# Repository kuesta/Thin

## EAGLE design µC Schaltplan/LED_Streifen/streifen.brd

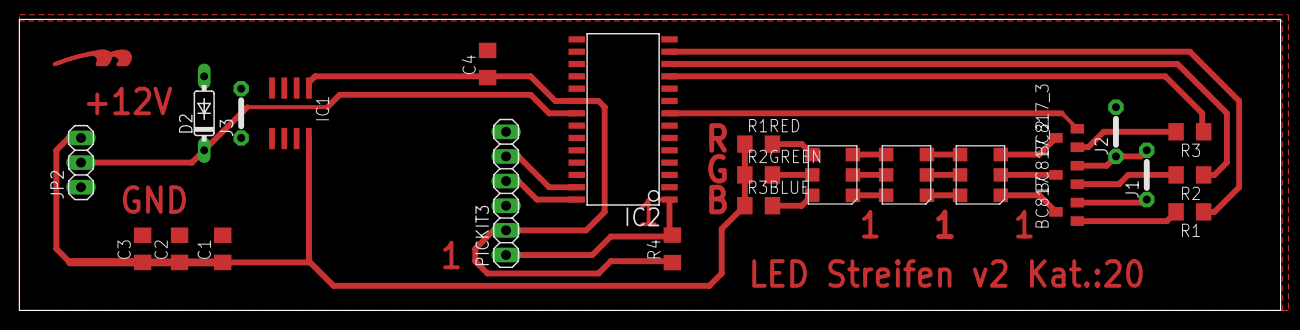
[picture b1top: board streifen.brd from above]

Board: 2 copper layers, 130.0 x 30.0 mm, 26 parts (0 on the bottom side), 27 nets.

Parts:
BC817, BC817_2, BC817_3: BC847SMD; SOT23
C1, C2, C3, C4: 100nF; C1206
D2: DO35-7
IC1: 78L05SMD; SO08
IC2: PIC18F2550_28W; SO28W
J1, J2, J3: J5MM; 05
JP2: 1X03
LED1, LED2, LED3: LP6-EWN1-03-N3; PLCC6
PICKIT3: 1X06
R1, R2, R3, R4: 1,2k; R1206
R1RED: 270; R1206
R2GREEN, R3BLUE: 100; R1206
U$1: LOGOTOP_8

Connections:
GND: BC817_3.2, C1.2, C2.2, C3.2, C4.2, D2.A, IC1.2, IC1.3, IC1.6, IC1.7, IC2.8, IC2.9, IC2.19, J2.2, J3.1, J3.2, JP2.1, PICKIT3.3
unnamed: BC817_3.3, LED1.PAD4
unnamed: IC2.13, R1.1
unnamed: D2.C, IC2.21, JP2.2
unnamed: IC2.1, PICKIT3.1, R4.2
unnamed: BC817_2.3, LED1.PAD5
unnamed: BC817.3, LED1.PAD6
unnamed: C4.1, IC1.1, IC2.20, PICKIT3.2, R4.1
unnamed: IC2.12, R2.1
unnamed: IC2.11, R3.1
unnamed: LED1.PAD3, LED2.PAD6
unnamed: LED1.PAD2, LED2.PAD5
unnamed: LED1.PAD1, LED2.PAD4
unnamed: LED2.PAD3, LED3.PAD6
unnamed: LED2.PAD2, LED3.PAD5
unnamed: LED2.PAD1, LED3.PAD4
unnamed: C1.1, C2.1, C3.1, IC1.8, JP2.3, R1RED.1, R2GREEN.1, R3BLUE.1
unnamed: LED3.PAD1, R1RED.2
unnamed: LED3.PAD2, R2GREEN.2
unnamed: LED3.PAD3, R3BLUE.2
unnamed: BC817.1, R1.2
unnamed: BC817_2.1, R2.2
unnamed: BC817_3.1, R3.2
unnamed: IC2.28, PICKIT3.4
unnamed: IC2.27, PICKIT3.5
unnamed: BC817_2.2, J1.2, J2.1
unnamed: BC817.2, J1.1

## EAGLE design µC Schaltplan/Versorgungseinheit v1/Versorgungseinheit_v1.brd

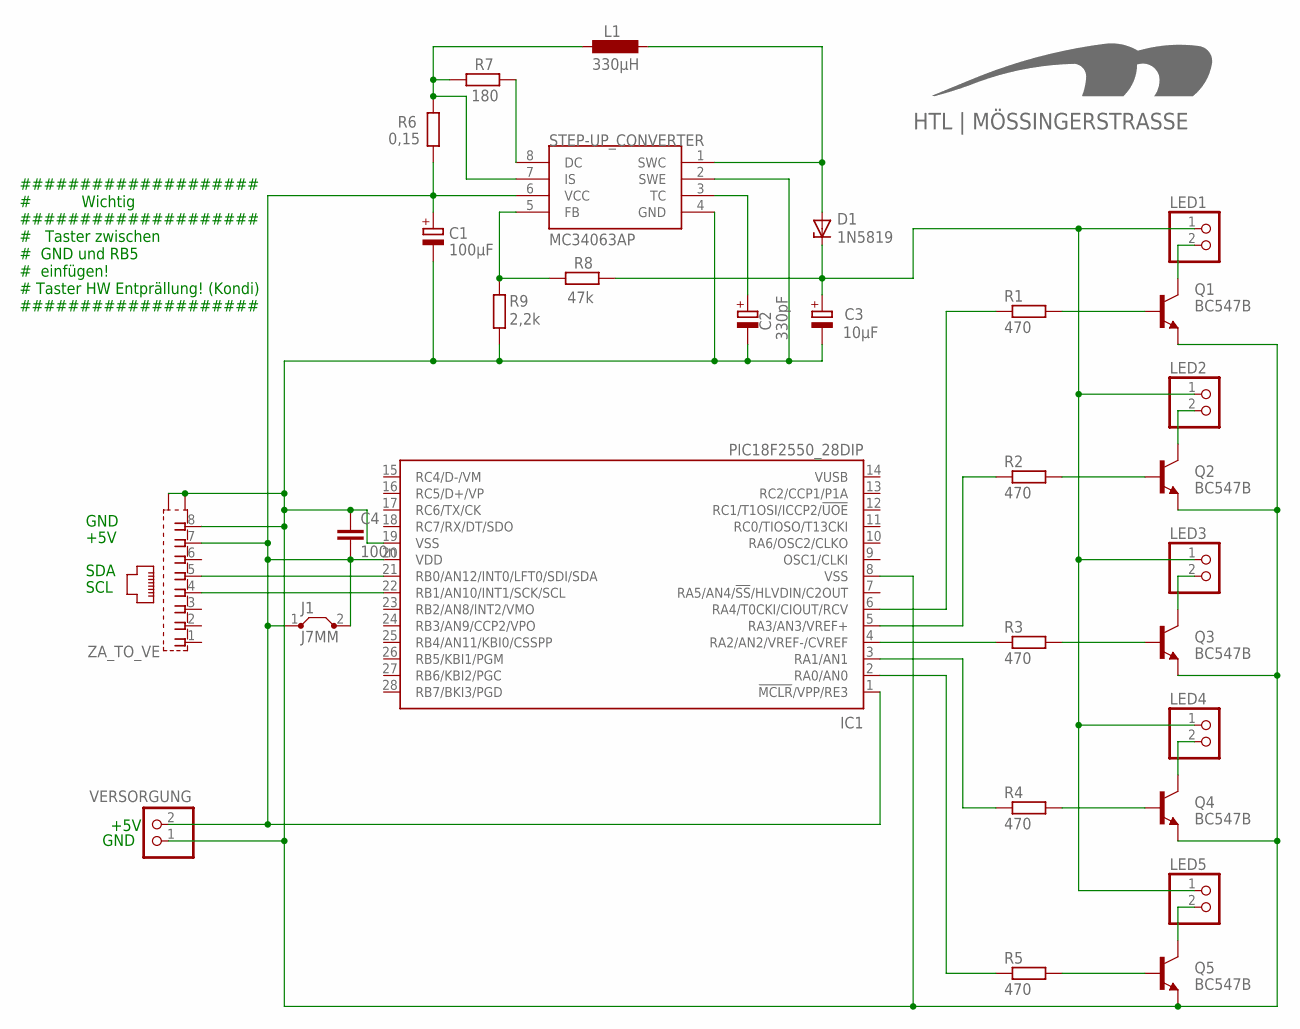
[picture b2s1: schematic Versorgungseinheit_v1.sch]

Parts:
C1: 100µF; E5-8,5
C2: 330pF; E5-8,5
C3: 10µF; E5-8,5
C4: 100n; C050-025X075
D1: 1N5819; DO41Z10
IC1: PIC18F2550_28DIP; DIL28-3
J1: J7MM; 07
L1: 330µH; 0207/10
LED1, LED2, LED3, LED4, LED5: PINHD-1X2; 1X02
Q1, Q2, Q3, Q4, Q5: BC547B; TO92
R1, R2, R3, R4, R5: 470; 0207/10
R6: 0,15; R1206
R7: 180; 0207/10
R8: 47k; 0207/10
R9: 2,2k; 0207/10
STEP-UP_CONVERTER: MC34063AP; DIL08
U$2: HTL_LOGOBOT_15MM; LOGOBOT_15
VERSORGUNG: PINHD-1X2; 1X02
ZA_TO_VE: 555141-1; 555153-1

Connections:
unnamed: IC1.2 (RA0/AN0), R5.1
unnamed: IC1.3 (RA1/AN1), R4.1
unnamed: IC1.6 (RA4/T0CKI/CIOUT/RCV), R1.1
unnamed: IC1.4 (RA2/AN2/VREF-/CVREF), R3.1
unnamed: C3.+, D1.C, LED1.1, LED2.1, LED3.1, LED4.1, LED5.1, R8.1
unnamed: IC1.5 (RA3/AN3/VREF+), R2.1
unnamed: IC1.22 (RB1/AN10/INT1/SCK/SCL), ZA_TO_VE.4
unnamed: Q1.2 (B), R1.2
unnamed: Q2.2 (B), R2.2
unnamed: Q3.2 (B), R3.2
unnamed: Q4.2 (B), R4.2
unnamed: Q5.2 (B), R5.2
unnamed: LED1.2, Q1.3 (C)
unnamed: LED2.2, Q2.3 (C)
unnamed: LED3.2, Q3.3 (C)
unnamed: LED4.2, Q4.3 (C)
unnamed: LED5.2, Q5.3 (C)
unnamed: L1.2, R6.2, R7.2, STEP-UP_CONVERTER.7 (IS)
unnamed: R7.1, STEP-UP_CONVERTER.8 (DC)
unnamed: D1.A, L1.1, STEP-UP_CONVERTER.1 (SWC)
unnamed: R8.2, R9.1, STEP-UP_CONVERTER.5 (FB)
unnamed: C2.+, STEP-UP_CONVERTER.3 (TC)
SDA: IC1.21 (RB0/AN12/INT0/LFT0/SDI/SDA), ZA_TO_VE.5
VDD: C1.+, C4.2, IC1.1 (!MCLR!/VPP/RE3), IC1.20 (VDD), J1.1, J1.2, R6.1, STEP-UP_CONVERTER.6 (VCC), VERSORGUNG.2, ZA_TO_VE.7
VSS: C1.-, C2.-, C3.-, C4.1, IC1.8 (VSS), IC1.19 (VSS), Q1.1 (E), Q2.1 (E), Q3.1 (E), Q4.1 (E), Q5.1 (E), R9.2, STEP-UP_CONVERTER.2 (SWE), STEP-UP_CONVERTER.4 (GND), VERSORGUNG.1, ZA_TO_VE.8, ZA_TO_VE.G1 (S1), ZA_TO_VE.G2 (S2)

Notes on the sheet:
GND
+5V
SCL
SDA
#################### # Wichtig #################### # Taster zwischen # GND und RB5 # einfügen! # Taster HW Entprällung! (Kondi) ####################

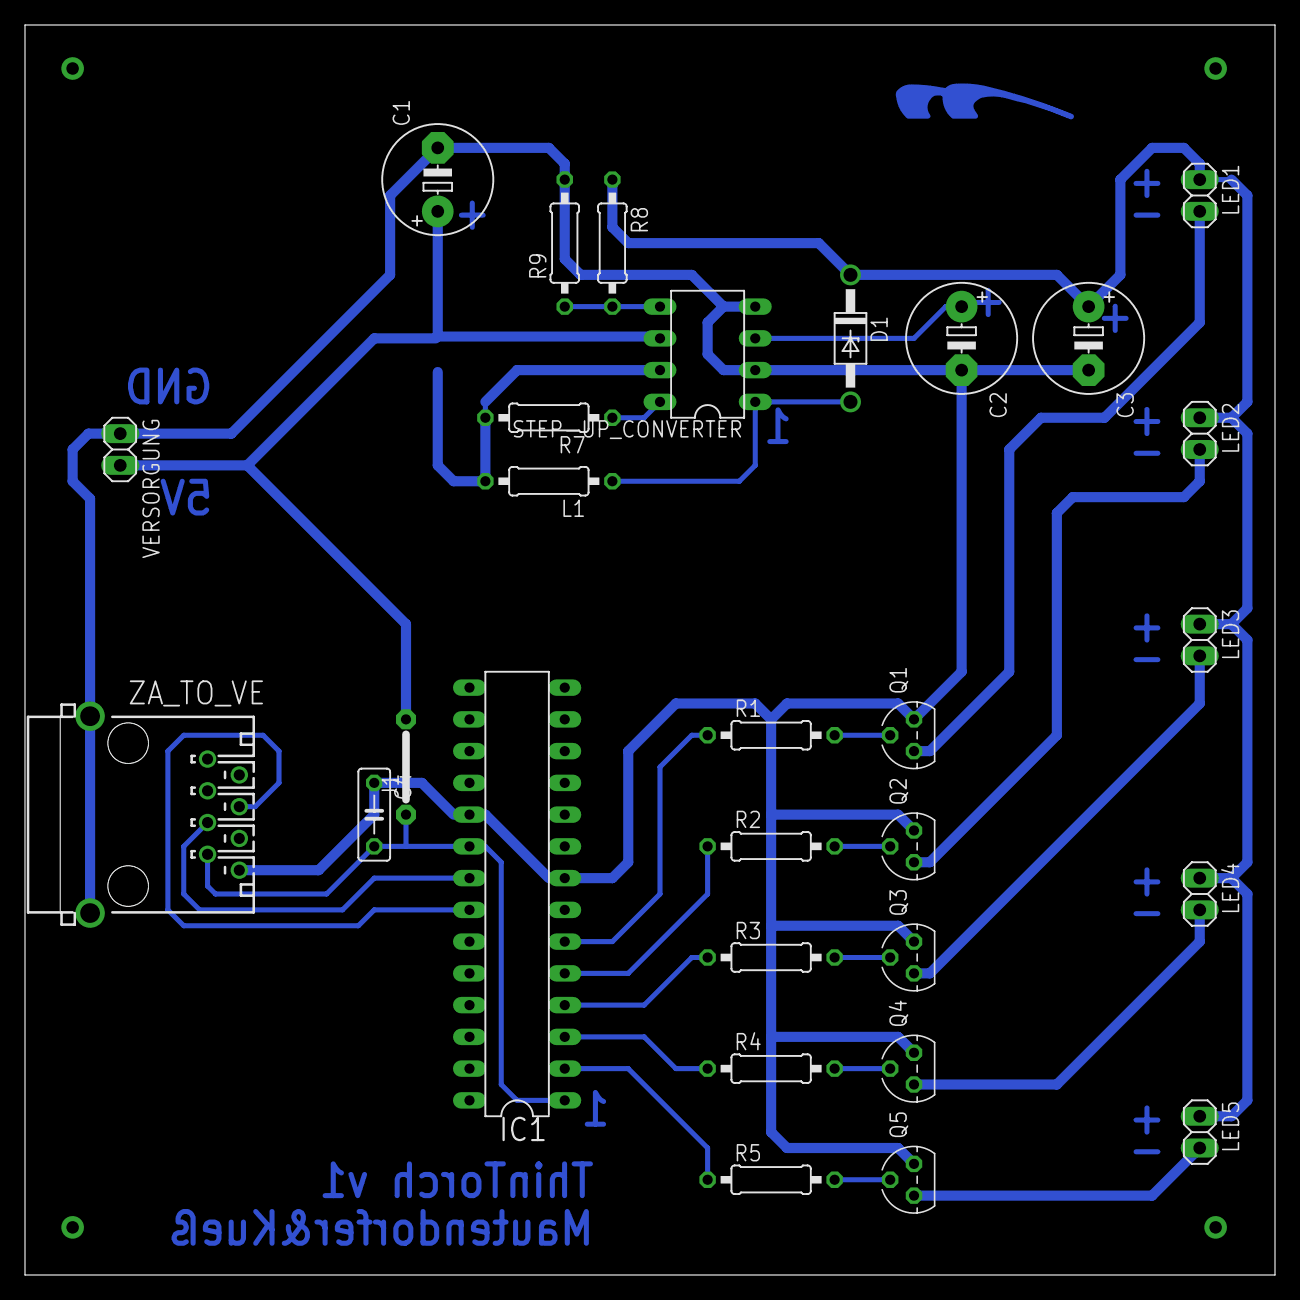
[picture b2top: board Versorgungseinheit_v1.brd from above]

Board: 2 copper layers, 100.0 x 100.0 mm, 31 parts (1 on the bottom side), 25 nets.

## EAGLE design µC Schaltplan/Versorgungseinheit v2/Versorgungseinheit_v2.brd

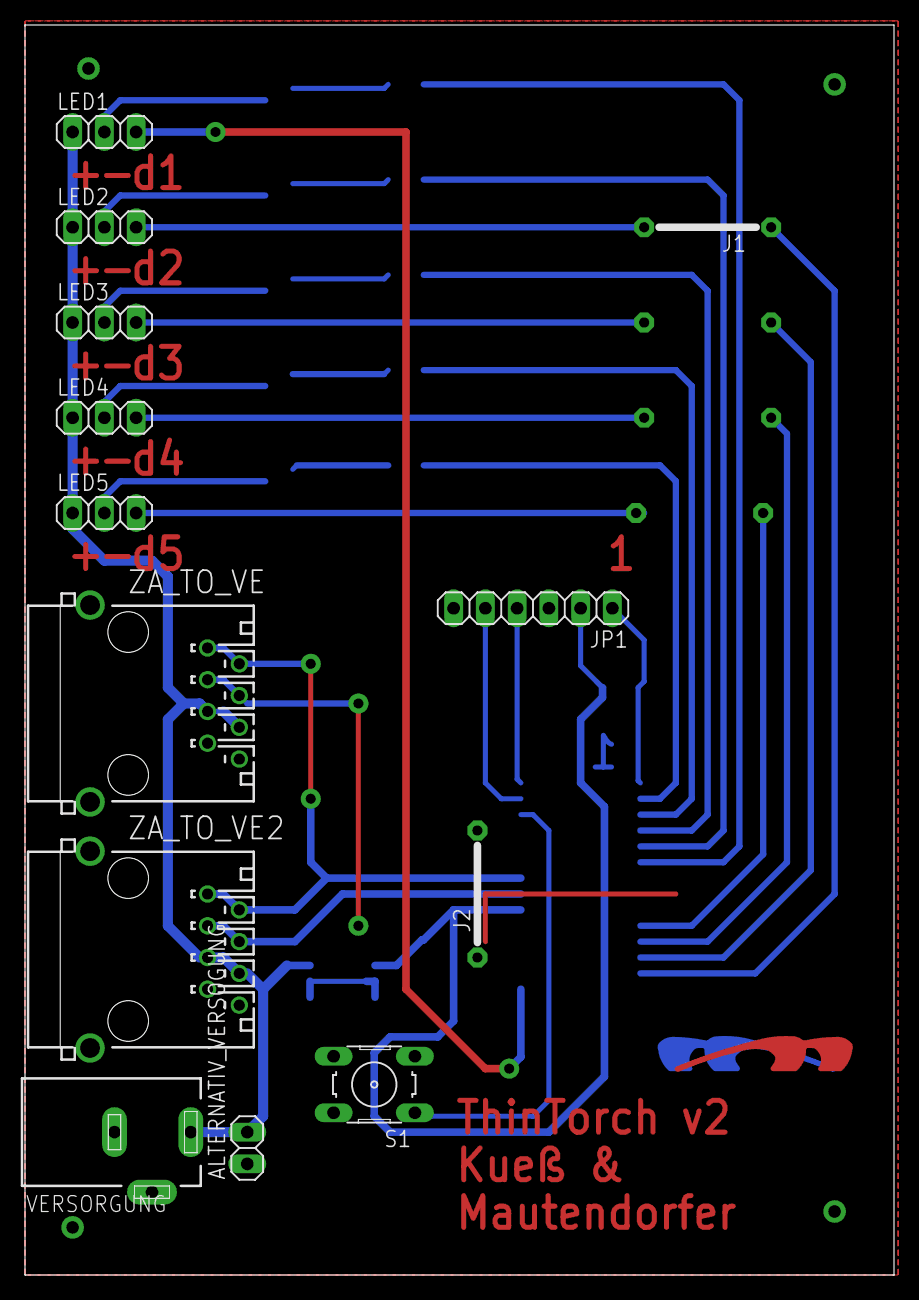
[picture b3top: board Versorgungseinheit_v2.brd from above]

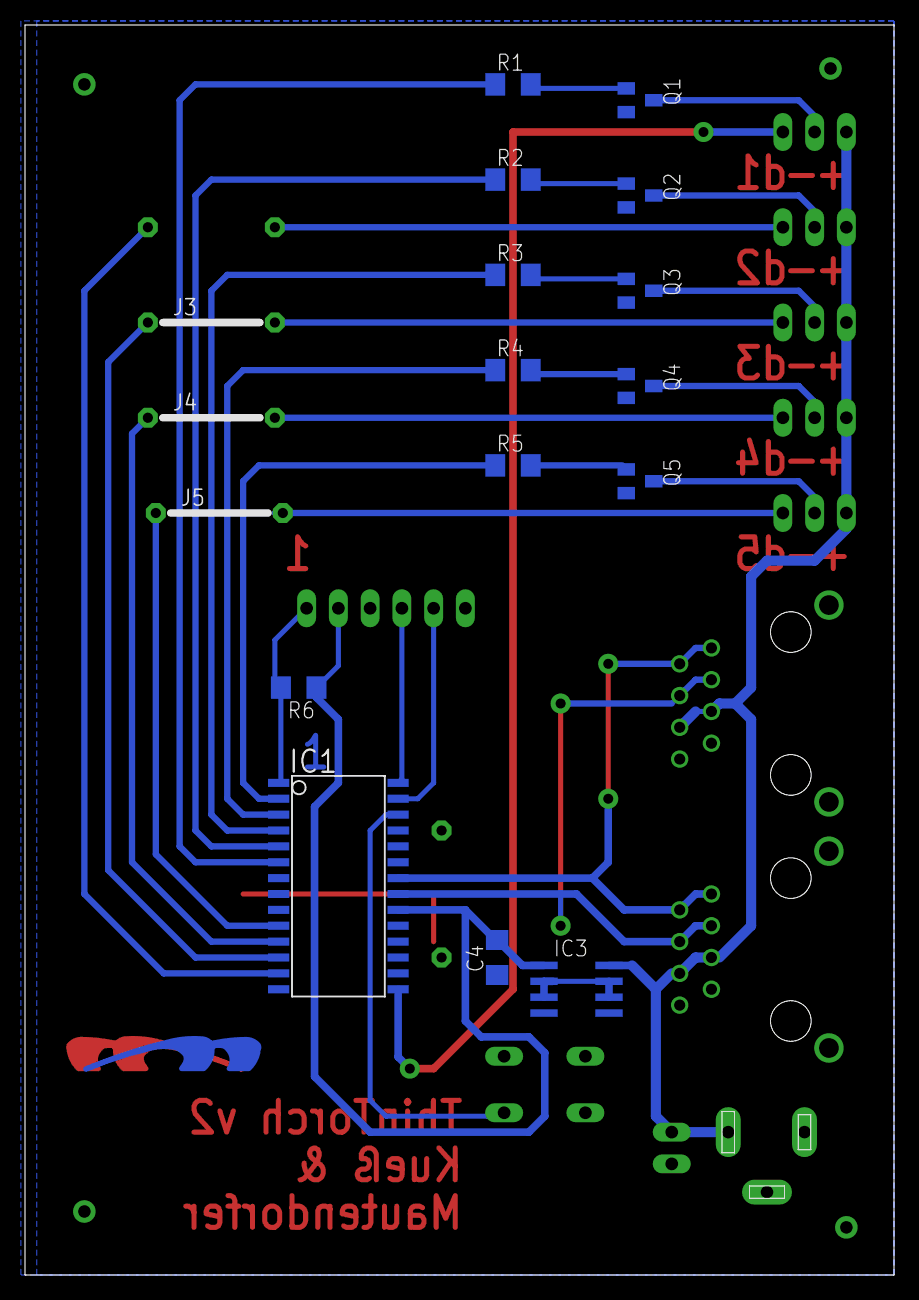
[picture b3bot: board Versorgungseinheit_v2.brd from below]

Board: 2 copper layers, 69.5 x 100.0 mm, 31 parts (17 on the bottom side), 33 nets.

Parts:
ALTERNATIV_VERSOGUNG: 12V; 1X02
C4: 100n; C1206
IC1: PIC18F2455_28W; SO28W
IC3: 78L05SMD; SO08
J1, J2, J3, J4, J5: J10MM; 10
JP1: PicKit; 1X06
LED1, LED2, LED3, LED4, LED5: 1X03
Q1, Q2, Q3, Q4, Q5: BC847; SOT23
R1, R2, R3, R4, R5: 470; R1206
R6: 10k; R1206
S1: B3F-10XX
U$1: HTL_LOGOBOTTOP_15MM; LOGO_15
VERSORGUNG: 12V; DCJ0303
ZA_TO_VE, ZA_TO_VE2: 555153-1

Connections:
unnamed: IC1.2, R5.1
unnamed: IC1.3, R4.1
unnamed: IC1.6, R1.1
unnamed: IC1.4, R3.1
unnamed: IC1.26, S1.1
unnamed: IC1.5, R2.1
unnamed: J5.2, LED5.3
unnamed: Q1.1, R1.2
unnamed: Q2.1, R2.2
unnamed: Q3.1, R3.2
unnamed: Q4.1, R4.2
unnamed: Q5.1, R5.2
unnamed: LED1.2, Q1.3
unnamed: LED2.2, Q2.3
unnamed: LED3.2, Q3.3
unnamed: LED4.2, Q4.3
unnamed: LED5.2, Q5.3
unnamed: J4.2, LED4.3
unnamed: C4.2, IC1.20, IC3.1, JP1.2, R6.1
unnamed: J3.2, LED3.3
unnamed: IC1.13, J1.1
unnamed: IC1.15, LED1.3
unnamed: IC1.28, JP1.4
unnamed: IC1.27, JP1.5
unnamed: IC1.1, JP1.1, R6.2
unnamed: J1.2, LED2.3
unnamed: IC1.12, J3.1
unnamed: IC1.11, J4.1
unnamed: IC1.10, J5.1
SCL: IC1.22, ZA_TO_VE.1, ZA_TO_VE.2, ZA_TO_VE2.1, ZA_TO_VE2.2
SDA: IC1.21, ZA_TO_VE.3, ZA_TO_VE.4, ZA_TO_VE2.3, ZA_TO_VE2.4
VDD: ALTERNATIV_VERSOGUNG.2, IC3.8, LED1.1, LED2.1, LED3.1, LED4.1, LED5.1, VERSORGUNG.1, ZA_TO_VE.5, ZA_TO_VE.6, ZA_TO_VE2.5, ZA_TO_VE2.6
VSS: ALTERNATIV_VERSOGUNG.1, C4.1, IC1.8, IC1.19, IC3.2, IC3.3, IC3.6, IC3.7, J2.1, J2.2, JP1.3, Q1.2, Q2.2, Q3.2, Q4.2, Q5.2, S1.4, VERSORGUNG.2, VERSORGUNG.3, ZA_TO_VE.7, ZA_TO_VE.8, ZA_TO_VE.G1, ZA_TO_VE.G2, ZA_TO_VE2.7, ZA_TO_VE2.8, ZA_TO_VE2.G1, ZA_TO_VE2.G2

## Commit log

2014-03-03 create files
2014-03-03 Add TestCase
2014-03-03 Update errorbitmask
2014-03-03 update errorhandling testcase
2014-03-03 removed & commit code
2014-03-03 create LED-Streifen v1
2014-03-03 create Firmware Versorgrungseinheit V1
2014-03-06 moved
2014-03-06 renamed
2014-03-06 create ZentralEinheit v1 Files
2014-03-06 removed useless code
2014-03-06 Add Binary v1
2014-03-06 moved in Software
2014-03-06 added in Repo
2014-03-06 Added to Repo
2014-03-10 update data input
2014-03-10 Demoprogramm for connecting to the pic
2014-03-10 adding axtra parameter (verlauf)
2014-03-10 cleanup
2014-03-13 update to v3
2014-03-13 modifyed code
2014-03-13 edit
2014-03-17 update (menue)
